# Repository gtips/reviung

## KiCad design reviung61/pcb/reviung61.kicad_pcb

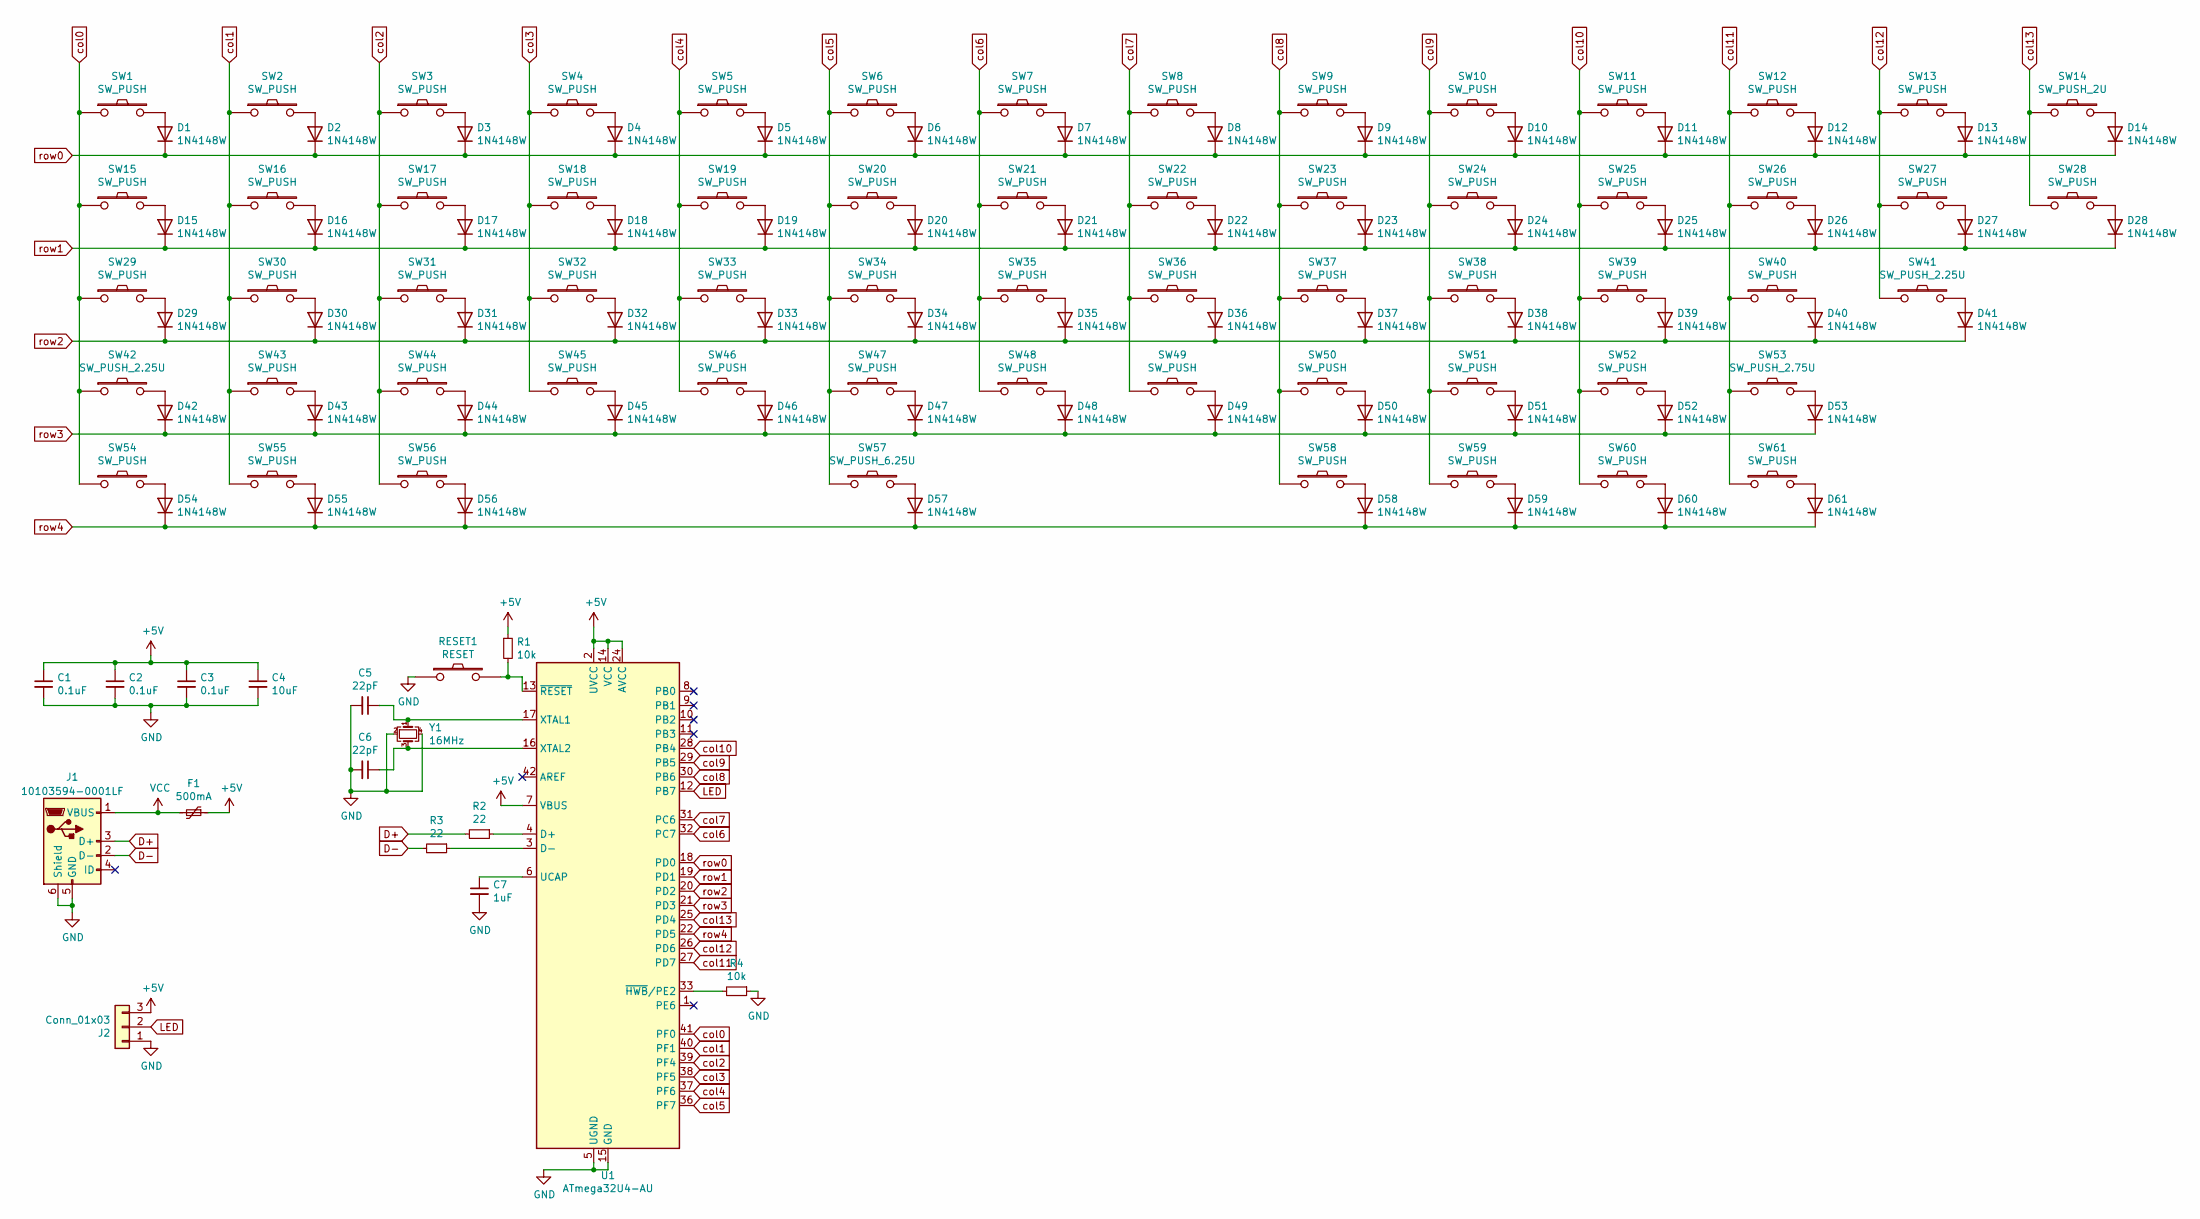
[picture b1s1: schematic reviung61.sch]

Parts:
C1, C2, C3: 0.1uF; C_1206_3216Metric_Pad1.42x1.75mm_HandSolder
C4: 10uF; C_1206_3216Metric_Pad1.42x1.75mm_HandSolder
C5, C6: 22pF; C_1206_3216Metric_Pad1.42x1.75mm_HandSolder
C7: 1uF; C_1206_3216Metric_Pad1.42x1.75mm_HandSolder
D1, D2, D3, D4, D5, D6, D7, D8, D9, D10, D11, D12, D13, D14, D15, D16, D17, D18, D19, D20, D21, D22, D23, D24, D25, D26, D27, D28, D29, D30, D31, D32, D33, D34, D35, D36, D37, D38, D39, D40, D41, D42, D43, D44, D45, D46, D47, D48, D49, D50, D51, D52, D53, D54, D55, D56, D57, D58, D59, D60, D61: 1N4148W; D3_TH_SMD_1side
F1: 500mA; Fuse_0805_2012Metric_Pad1.15x1.40mm_HandSolder
J1: 10103594-0001LF; USB_Micro-B_Amphenol_10103594-0001LF_Horizontal
J2: Conn_01x03; StripLED_1side
R1, R4: 10k; R_1206_3216Metric_Pad1.42x1.75mm_HandSolder
R2, R3: 22; R_1206_3216Metric_Pad1.42x1.75mm_HandSolder
RESET1: RESET; ResetSW_1side
SW1, SW2, SW3, SW4, SW5, SW6, SW7, SW8, SW9, SW10, SW11, SW12, SW13, SW15, SW16, SW17, SW18, SW19, SW20, SW21, SW22, SW23, SW24, SW25, SW26, SW27, SW28, SW29, SW30, SW31, SW32, SW33, SW34, SW35, SW36, SW37, SW38, SW39, SW40, SW43, SW44, SW45, SW46, SW47, SW48, SW49, SW50, SW51, SW52, SW54, SW55, SW56, SW58, SW59, SW60, SW61: SW_PUSH; MX-1U-NoLED
SW14: SW_PUSH_2U; MX-2U-NoLED
SW41, SW42: SW_PUSH_2.25U; MX-2.25U-NoLED
SW53: SW_PUSH_2.75U; MX-2.75U-NoLED
SW57: SW_PUSH_6.25U; MX-6.25U-ReversedStabilizers-NoLED
U1: ATmega32U4-AU; TQFP-44_10x10mm_P0.8mm
Y1: 16MHz; Crystal_SMD_3225-4Pin_3.2x2.5mm_HandSoldering

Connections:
+5V: C1.1, C2.1, C3.1, C4.1, F1.1, J2.3, R1.1, U1.2 (UVCC), U1.7 (VBUS), U1.14 (VCC), U1.24 (AVCC), U1.34 (VCC), U1.44 (AVCC)
D+: J1.3 (D+), R2.2
D-: J1.2 (D-), R3.2
GND: C1.2, C2.2, C3.2, C4.2, C5.2, C6.2, C7.2, J1.5 (GND), J1.6 (Shield), J2.1, R4.1, RESET1.1, U1.5 (UGND), U1.15 (GND), U1.23 (GND), U1.35 (GND), U1.43 (GND), Y1.2, Y1.4
LED: J2.2, U1.12 (PB7)
unnamed: C5.1, U1.17 (XTAL1), Y1.1
unnamed: C6.1, U1.16 (XTAL2), Y1.3
unnamed: C7.1, U1.6 (UCAP)
unnamed: D1.2 (A), SW1.2
unnamed: D2.2 (A), SW2.2
unnamed: D3.2 (A), SW3.2
unnamed: D4.2 (A), SW4.2
unnamed: D5.2 (A), SW5.2
unnamed: D6.2 (A), SW6.2
unnamed: D7.2 (A), SW7.2
unnamed: D8.2 (A), SW8.2
unnamed: D9.2 (A), SW9.2
unnamed: D10.2 (A), SW10.2
unnamed: D11.2 (A), SW11.2
unnamed: D12.2 (A), SW12.2
unnamed: D13.2 (A), SW13.2
unnamed: D14.2 (A), SW14.2
unnamed: D15.2 (A), SW15.2
unnamed: D16.2 (A), SW16.2
unnamed: D17.2 (A), SW17.2
unnamed: D18.2 (A), SW18.2
unnamed: D19.2 (A), SW19.2
unnamed: D20.2 (A), SW20.2
unnamed: D21.2 (A), SW21.2
unnamed: D22.2 (A), SW22.2
unnamed: D23.2 (A), SW23.2
unnamed: D24.2 (A), SW24.2
unnamed: D25.2 (A), SW25.2
unnamed: D26.2 (A), SW26.2
unnamed: D27.2 (A), SW27.2
unnamed: D28.2 (A), SW28.2
unnamed: D29.2 (A), SW29.2
unnamed: D30.2 (A), SW30.2
unnamed: D31.2 (A), SW31.2
unnamed: D32.2 (A), SW32.2
unnamed: D33.2 (A), SW33.2
unnamed: D34.2 (A), SW34.2
unnamed: D35.2 (A), SW35.2
unnamed: D36.2 (A), SW36.2
unnamed: D37.2 (A), SW37.2
unnamed: D38.2 (A), SW38.2
unnamed: D39.2 (A), SW39.2
unnamed: D40.2 (A), SW40.2
unnamed: D41.2 (A), SW41.2
unnamed: D42.2 (A), SW42.2
unnamed: D43.2 (A), SW43.2
unnamed: D44.2 (A), SW44.2
unnamed: D45.2 (A), SW45.2
unnamed: D46.2 (A), SW46.2
unnamed: D47.2 (A), SW47.2
unnamed: D48.2 (A), SW48.2
unnamed: D49.2 (A), SW49.2
unnamed: D50.2 (A), SW50.2
unnamed: D51.2 (A), SW51.2
unnamed: D52.2 (A), SW52.2
unnamed: D53.2 (A), SW53.2
unnamed: D54.2 (A), SW54.2
unnamed: D55.2 (A), SW55.2
unnamed: D56.2 (A), SW56.2
unnamed: D57.2 (A), SW57.2
unnamed: D58.2 (A), SW58.2
unnamed: D59.2 (A), SW59.2
unnamed: D60.2 (A), SW60.2
unnamed: D61.2 (A), SW61.2
unnamed: R1.2, RESET1.2, U1.13 (~RESET)
unnamed: R2.1, U1.4 (D+)
unnamed: R3.1, U1.3 (D-)
unnamed: R4.2, U1.33 (~HWB~/PE2)
VCC: F1.2, J1.1 (VBUS)
col0: SW1.1, SW15.1, SW29.1, SW42.1, SW54.1, U1.41 (PF0)
col1: SW2.1, SW16.1, SW30.1, SW43.1, SW55.1, U1.40 (PF1)
col2: SW3.1, SW17.1, SW31.1, SW44.1, SW56.1, U1.39 (PF4)
col3: SW4.1, SW18.1, SW32.1, SW45.1, U1.38 (PF5)
col4: SW5.1, SW19.1, SW33.1, SW46.1, U1.37 (PF6)
col5: SW6.1, SW20.1, SW34.1, SW47.1, SW57.1, U1.36 (PF7)
col6: SW7.1, SW21.1, SW35.1, SW48.1, U1.32 (PC7)
col7: SW8.1, SW22.1, SW36.1, SW49.1, U1.31 (PC6)
col8: SW9.1, SW23.1, SW37.1, SW50.1, SW58.1, U1.30 (PB6)
col9: SW10.1, SW24.1, SW38.1, SW51.1, SW59.1, U1.29 (PB5)
col10: SW11.1, SW25.1, SW39.1, SW52.1, SW60.1, U1.28 (PB4)
col11: SW12.1, SW26.1, SW40.1, SW53.1, SW61.1, U1.27 (PD7)
col12: SW13.1, SW27.1, SW41.1, U1.26 (PD6)
col13: SW14.1, SW28.1, U1.25 (PD4)
row0: D1.1 (K), D2.1 (K), D3.1 (K), D4.1 (K), D5.1 (K), D6.1 (K), D7.1 (K), D8.1 (K), D9.1 (K), D10.1 (K), D11.1 (K), D12.1 (K), D13.1 (K), D14.1 (K), U1.18 (PD0)
row1: D15.1 (K), D16.1 (K), D17.1 (K), D18.1 (K), D19.1 (K), D20.1 (K), D21.1 (K), D22.1 (K), D23.1 (K), D24.1 (K), D25.1 (K), D26.1 (K), D27.1 (K), D28.1 (K), U1.19 (PD1)
row2: D29.1 (K), D30.1 (K), D31.1 (K), D32.1 (K), D33.1 (K), D34.1 (K), D35.1 (K), D36.1 (K), D37.1 (K), D38.1 (K), D39.1 (K), D40.1 (K), D41.1 (K), U1.20 (PD2)
row3: D42.1 (K), D43.1 (K), D44.1 (K), D45.1 (K), D46.1 (K), D47.1 (K), D48.1 (K), D49.1 (K), D50.1 (K), D51.1 (K), D52.1 (K), D53.1 (K), U1.21 (PD3)
row4: D54.1 (K), D55.1 (K), D56.1 (K), D57.1 (K), D58.1 (K), D59.1 (K), D60.1 (K), D61.1 (K), U1.22 (PD5)

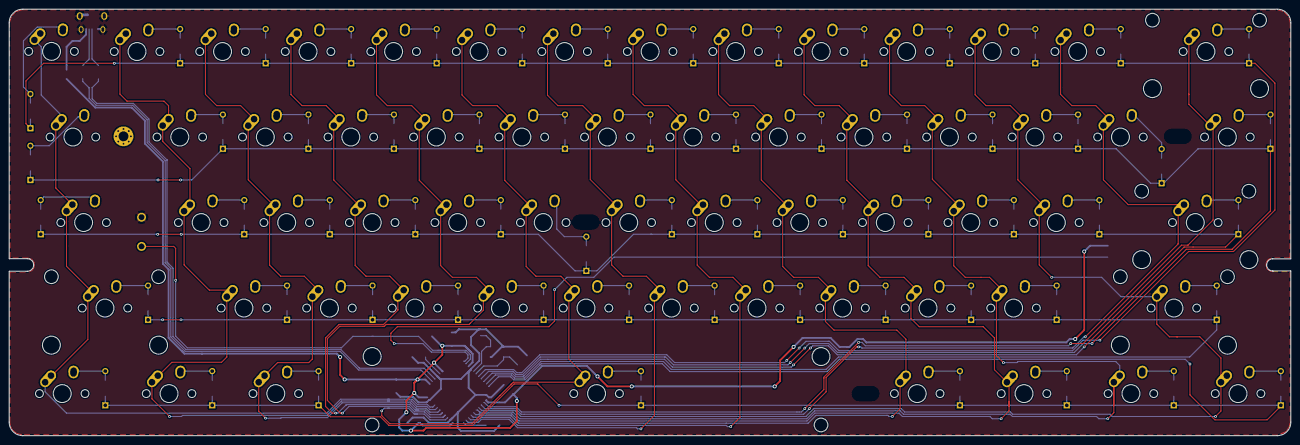
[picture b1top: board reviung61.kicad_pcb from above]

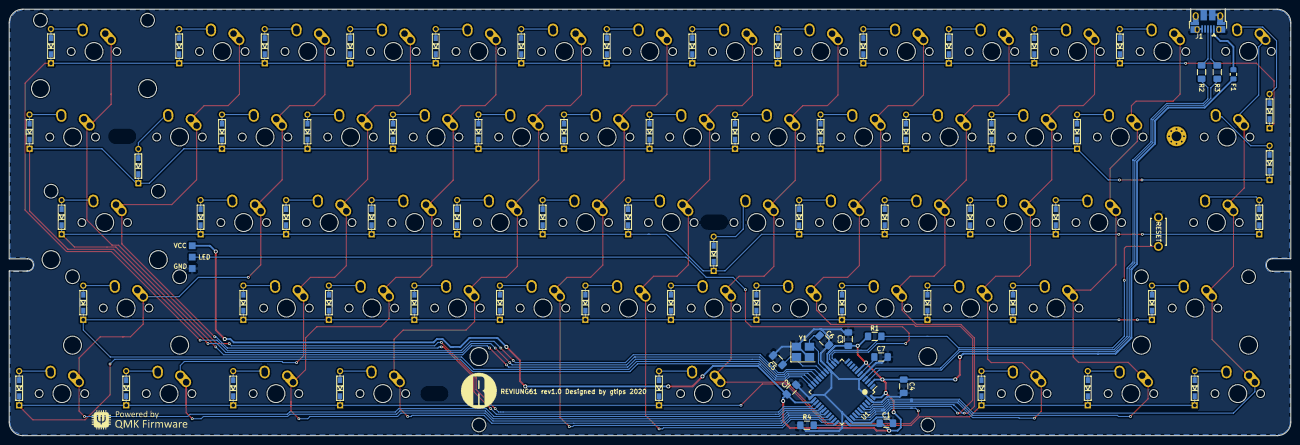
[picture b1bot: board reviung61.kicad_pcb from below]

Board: 2 copper layers, 285.5 x 95.0 mm, 143 parts (78 on the bottom side), 93 nets.

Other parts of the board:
H1: MountingHole_2.2mm_M2_Pad_Via
H2, H3, H4: HOLE_2.2mm_5.0mm
